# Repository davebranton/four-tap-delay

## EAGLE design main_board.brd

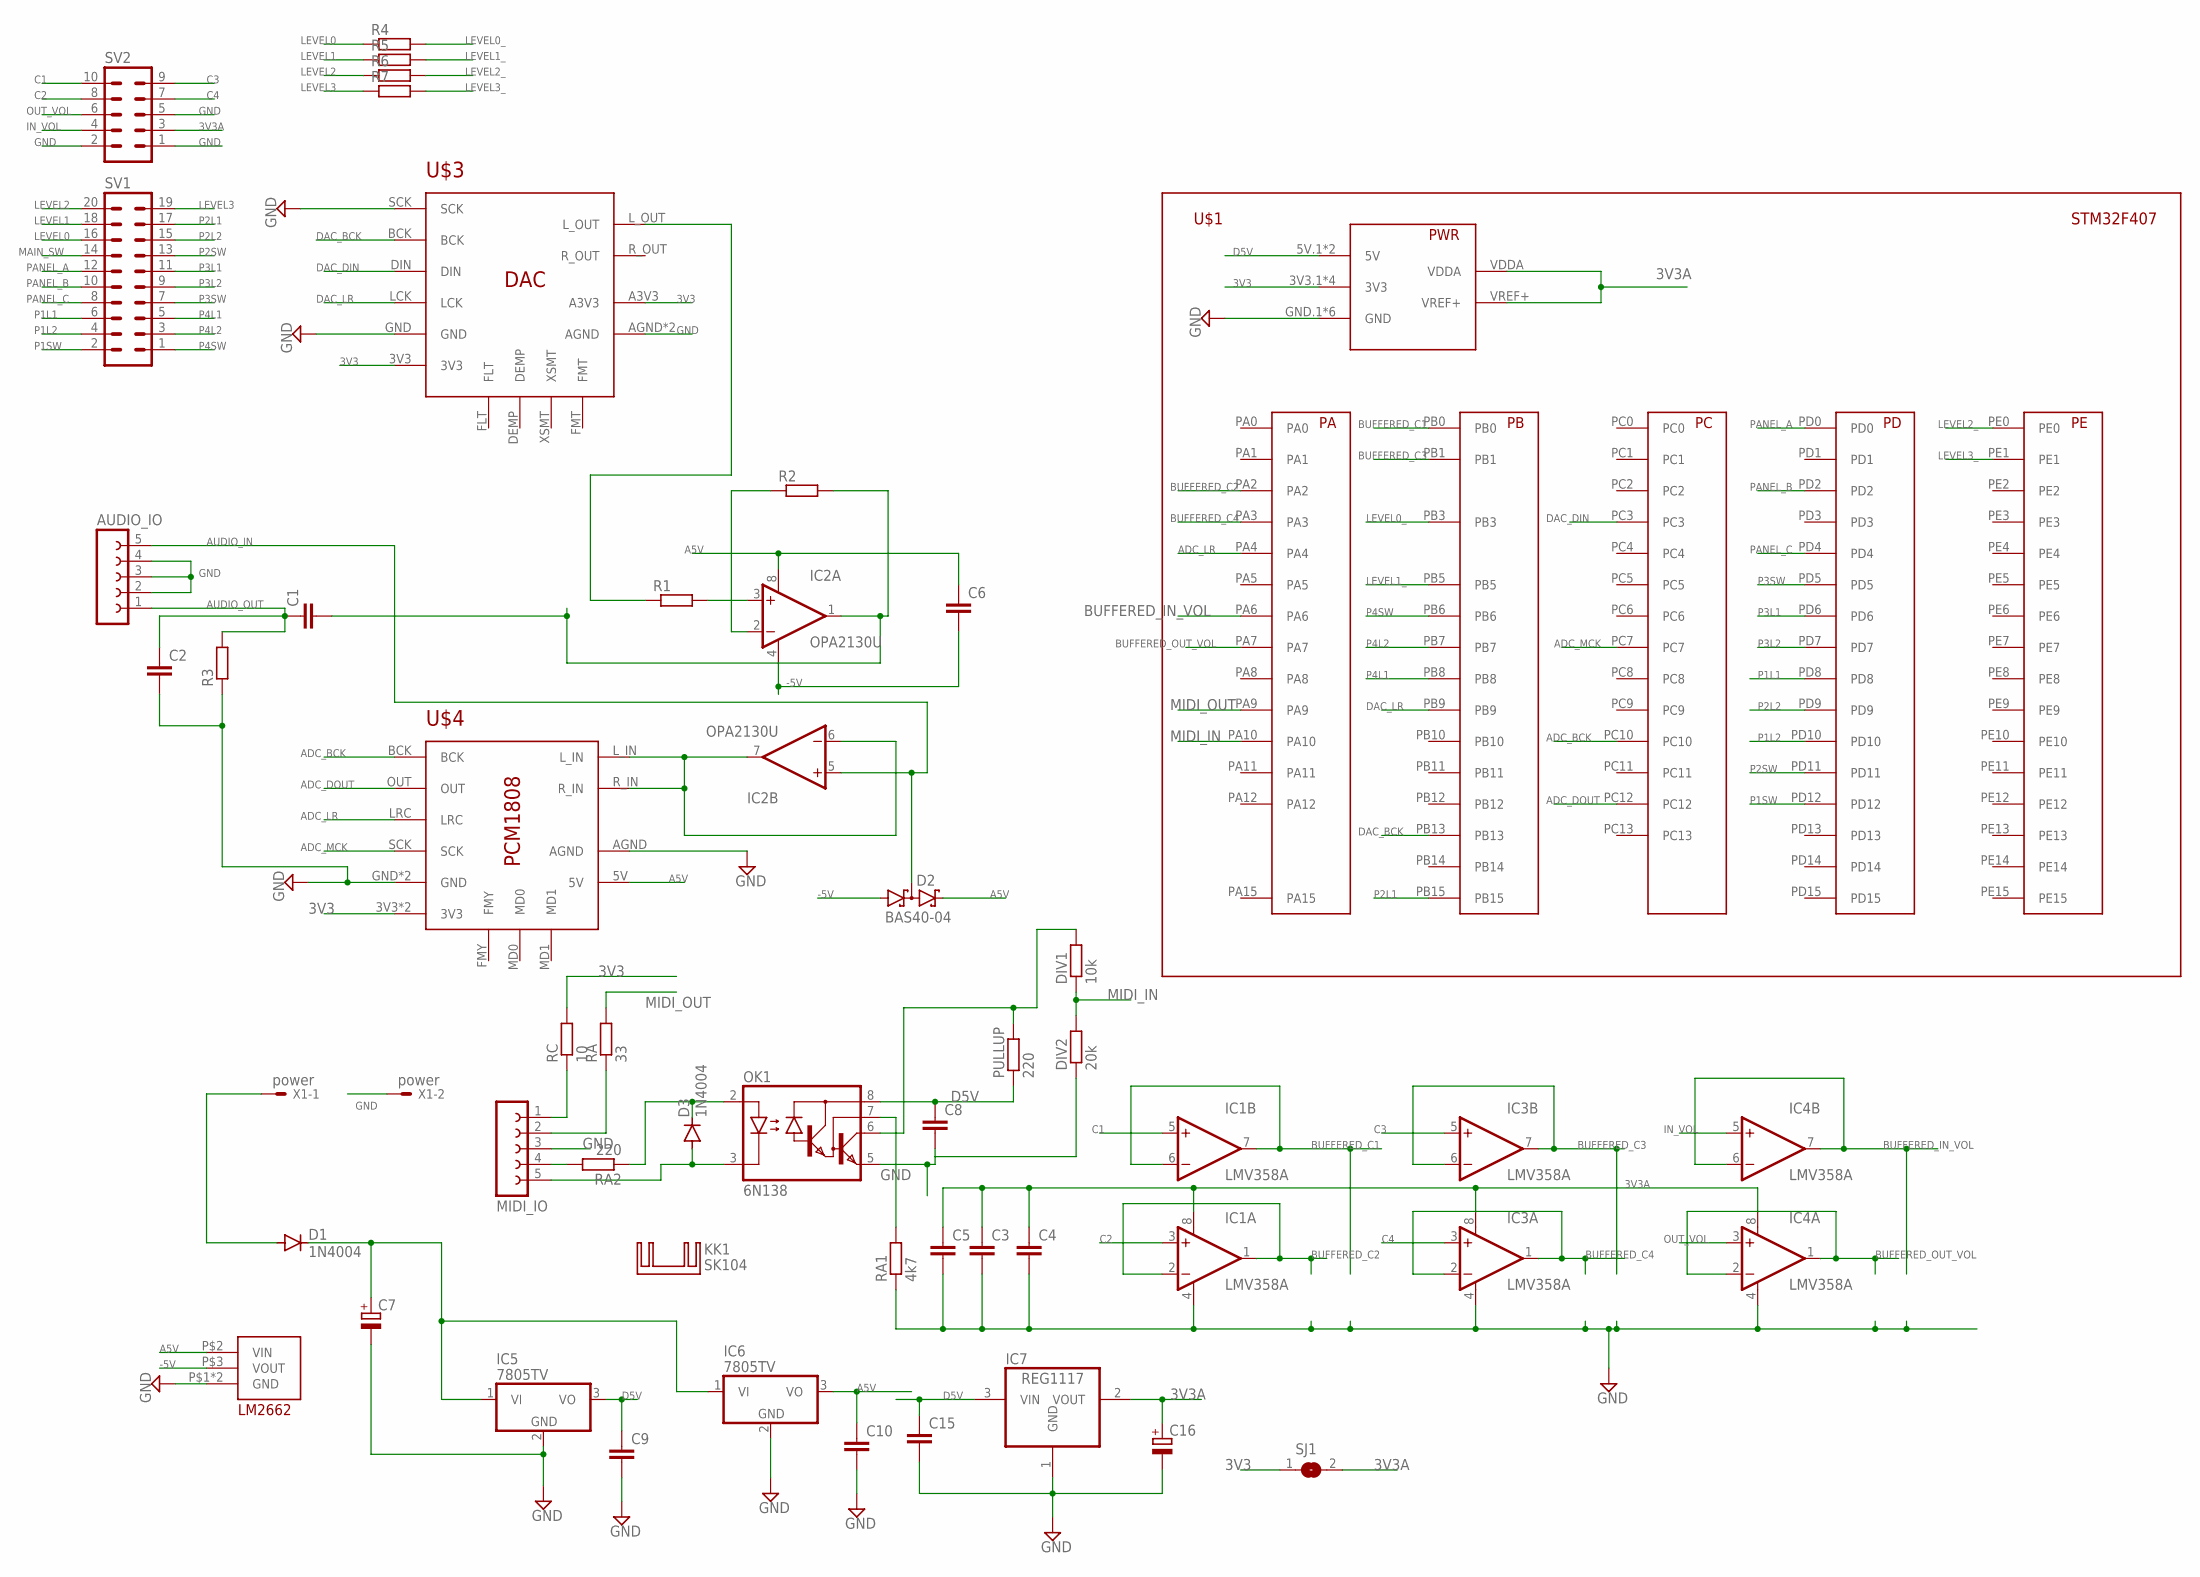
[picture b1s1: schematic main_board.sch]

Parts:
AUDIO_IO: FE05-1
C1: C5/5.5; C5B5.5
C2: C2,5-3; C2.5-3
C3, C4, C5, C6, C15: C-EUC0402; C0402
C7: CPOL-EUE2.5-7; E2,5-7
C8, C9, C10: C-EU025-024X044; C025-024X044
C16: CPOL-EUTT2D6L; TT2D6L
D1, D3: 1N4004; DO41-10
D2: BAS40-04; SOT23
DIV1: 10k; 0204V
DIV2: 20k; 0204V
IC1, IC3, IC4: LMV358A; SO08
IC2: OPA2130U; SO08
IC5, IC6: 7805TV; TO220V
IC7: REG1117; SOT223
KK1: SK104
MIDI_IO: FE05-1
OK1: 6N138; DIL08
PULLUP: 220; 0204V
R1, R2, R3: R-EU_0204/2V; 0204V
R4, R5, R6, R7: R-EU_R0402; R0402
RA: 33; 0204V
RA1: 4k7; 0204V
RA2: 220; 0204V
RC: 10; 0204V
SJ1: SJ
SV1: MA10-2
SV2: MA05-2
U$1: DEVEBOX
U$2: LM2662_MODULE
U$3: PCM510XA; DAC_MODULE
U$4: PCM1808; ADC_MODULE
X1: power; 332-02

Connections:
3V3: RC.2, SJ1.1, U$1.3V3.1 (3V3), U$1.3V3.2 (3V3), U$1.3V3.3 (3V3), U$1.3V3.4 (3V3), U$3.3V3, U$3.A3V3, U$4.3V3, U$4.3V3.1 (3V3)
3V3A: C3.1, C4.1, C5.1, C16.+, IC1.8 (V+), IC3.8 (V+), IC4.8 (V+), IC7.2 (VOUT), SJ1.2, SV2.3, U$1.VDDA, U$1.VREF+
-5V: C6.2, D2.1 (A1), IC2.4 (V-), U$2.P$3 (VOUT)
A5V: C6.1, C10.1, D2.2 (C2), IC2.8 (V+), IC6.3 (VO), U$2.P$2 (VIN), U$4.5V
ADC_BCK: U$1.PC10, U$4.BCK
ADC_DOUT: U$1.PC12, U$4.OUT
ADC_LR: U$1.PA4, U$4.LRC
ADC_MCK: U$1.PC7, U$4.SCK
AUDIO_IN: AUDIO_IO.5, D2.3 (C1A2), IC2.5 (+IN)
AUDIO_OUT: R1.1, U$3.L_OUT
BUFFERED_C1: IC1.6 (-IN), IC1.7 (OUT), U$1.PB0
BUFFERED_C2: IC1.1 (OUT), IC1.2 (-IN), U$1.PA2
BUFFERED_C3: IC3.6 (-IN), IC3.7 (OUT), U$1.PB1
BUFFERED_C4: IC3.1 (OUT), IC3.2 (-IN), U$1.PA3
BUFFERED_IN_VOL: IC4.6 (-IN), IC4.7 (OUT), U$1.PA6
BUFFERED_OUT_VOL: IC4.1 (OUT), IC4.2 (-IN), U$1.PA7
C1: IC1.5 (+IN), SV2.10
C2: IC1.3 (+IN), SV2.8
C3: IC3.5 (+IN), SV2.9
C4: IC3.3 (+IN), SV2.7
D5V: C8.1, C9.1, C15.1, IC5.3 (VO), IC7.3 (VIN), OK1.8 (VCC), PULLUP.1, U$1.5V.1 (5V), U$1.5V.2 (5V)
DAC_BCK: U$1.PB13, U$3.BCK
DAC_DIN: U$1.PC3, U$3.DIN
DAC_LR: U$1.PB9, U$3.LCK
GND: AUDIO_IO.2, AUDIO_IO.3, AUDIO_IO.4, C2.2, C3.2, C4.2, C5.2, C7.-, C8.2, C9.2, C10.2, C15.2, C16.-, DIV2.1, IC1.4 (V-), IC3.4 (V-), IC4.4 (V-), IC5.2 (GND), IC6.2 (GND), IC7.1 (GND), MIDI_IO.3, OK1.5 (GND), R3.1, RA1.1, SV2.1, SV2.2, SV2.5, U$1.GND4. (GND), U$1.GND.1 (GND), U$1.GND.2 (GND), U$1.GND.3 (GND), U$1.GND.6 (GND), U$1.GND.7 (GND), U$2.P$1 (GND), U$2.P$4 (GND), U$3.AGND, U$3.AGND.1 (AGND), U$3.GND, U$3.SCK, U$4.AGND, U$4.GND, U$4.GND.1 (GND), X1.2
IN_VOL: IC4.5 (+IN), SV2.4
LEVEL0: R4.1, SV1.16
LEVEL0_: R4.2, U$1.PB3
LEVEL1: R5.1, SV1.18
LEVEL1_: R5.2, U$1.PB5
LEVEL2: R6.1, SV1.20
LEVEL2_: R6.2, U$1.PE0
LEVEL3: R7.1, SV1.19
LEVEL3_: R7.2, U$1.PE1
MAIN_SW: SV1.14
MIDI_IN: DIV1.1, DIV2.2, U$1.PA10
MIDI_OUT: RA.2, U$1.PA9
unnamed: C7.+, D1.C, IC5.1 (VI), IC6.1 (VI)
unnamed: IC2.6 (-IN), IC2.7 (OUT), U$4.L_IN, U$4.R_IN
unnamed: D1.A, X1.1
unnamed: AUDIO_IO.1, C1.1, C2.1, R3.2
unnamed: D3.A, MIDI_IO.5, OK1.3 (C)
unnamed: D3.C, OK1.2 (A), RA2.1
unnamed: DIV1.2, OK1.6 (VO), PULLUP.2
unnamed: MIDI_IO.1, RC.1
unnamed: MIDI_IO.2, RA.1
unnamed: IC2.3 (+IN), R1.2
unnamed: C1.2, IC2.1 (OUT), R2.2
unnamed: IC2.2 (-IN), R2.1
unnamed: OK1.7 (VB), RA1.2
unnamed: MIDI_IO.4, RA2.2
OUT_VOL: IC4.3 (+IN), SV2.6
P1L1: SV1.6, U$1.PD8
P1L2: SV1.4, U$1.PD10
P1SW: SV1.2, U$1.PD12
P2L1: SV1.17, U$1.PB15
P2L2: SV1.15, U$1.PD9
P2SW: SV1.13, U$1.PD11
P3L1: SV1.11, U$1.PD6
P3L2: SV1.9, U$1.PD7
P3SW: SV1.7, U$1.PD5
P4L1: SV1.5, U$1.PB8
P4L2: SV1.3, U$1.PB7
P4SW: SV1.1, U$1.PB6
PANEL_A: SV1.12, U$1.PD0
PANEL_B: SV1.10, U$1.PD2
PANEL_C: SV1.8, U$1.PD4

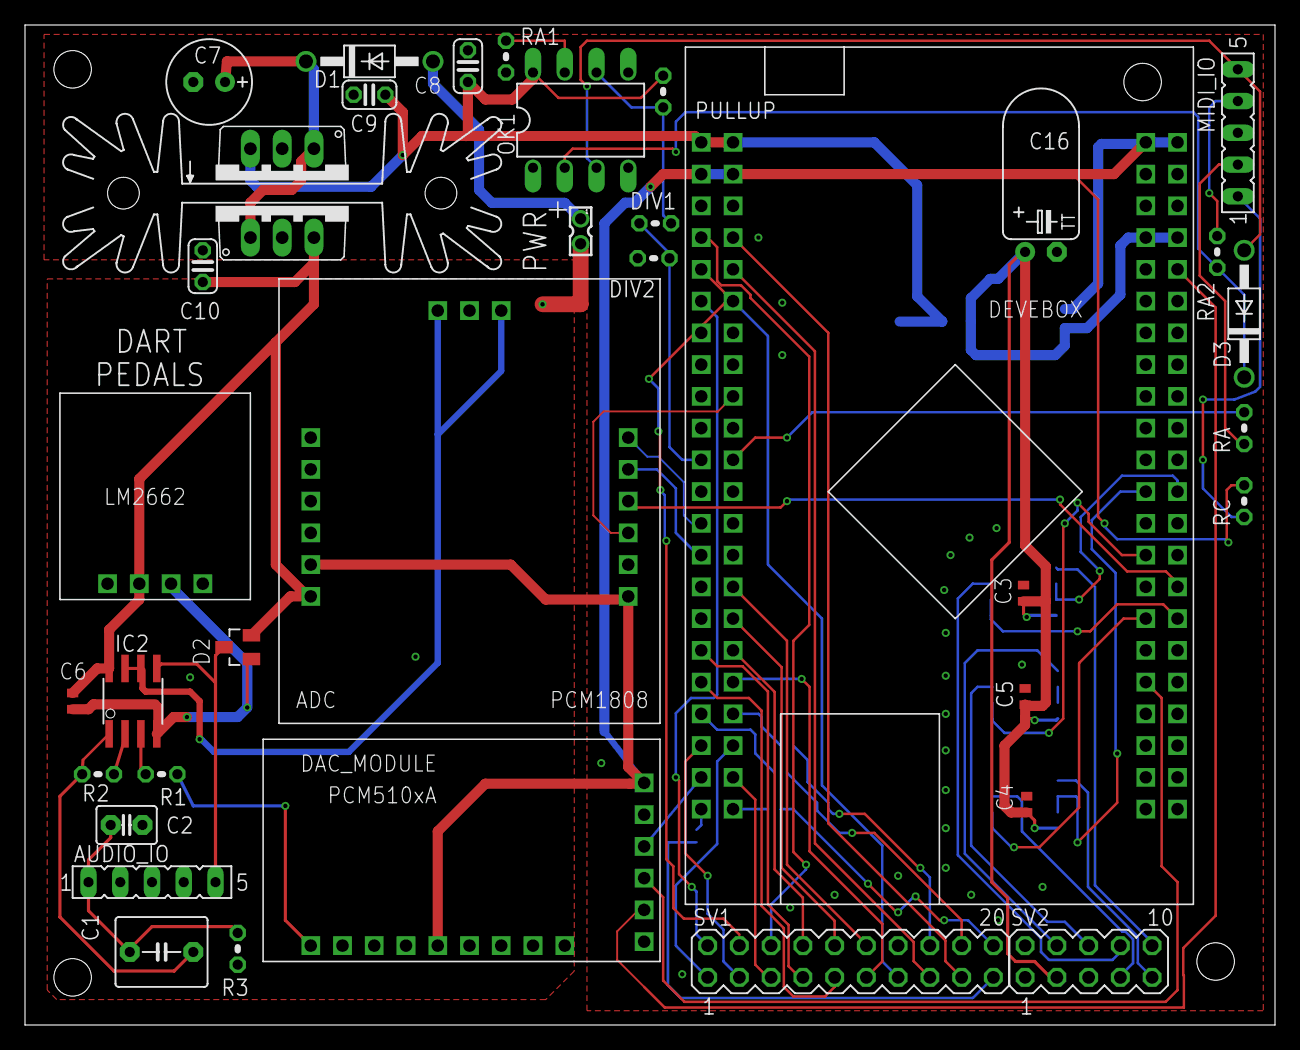
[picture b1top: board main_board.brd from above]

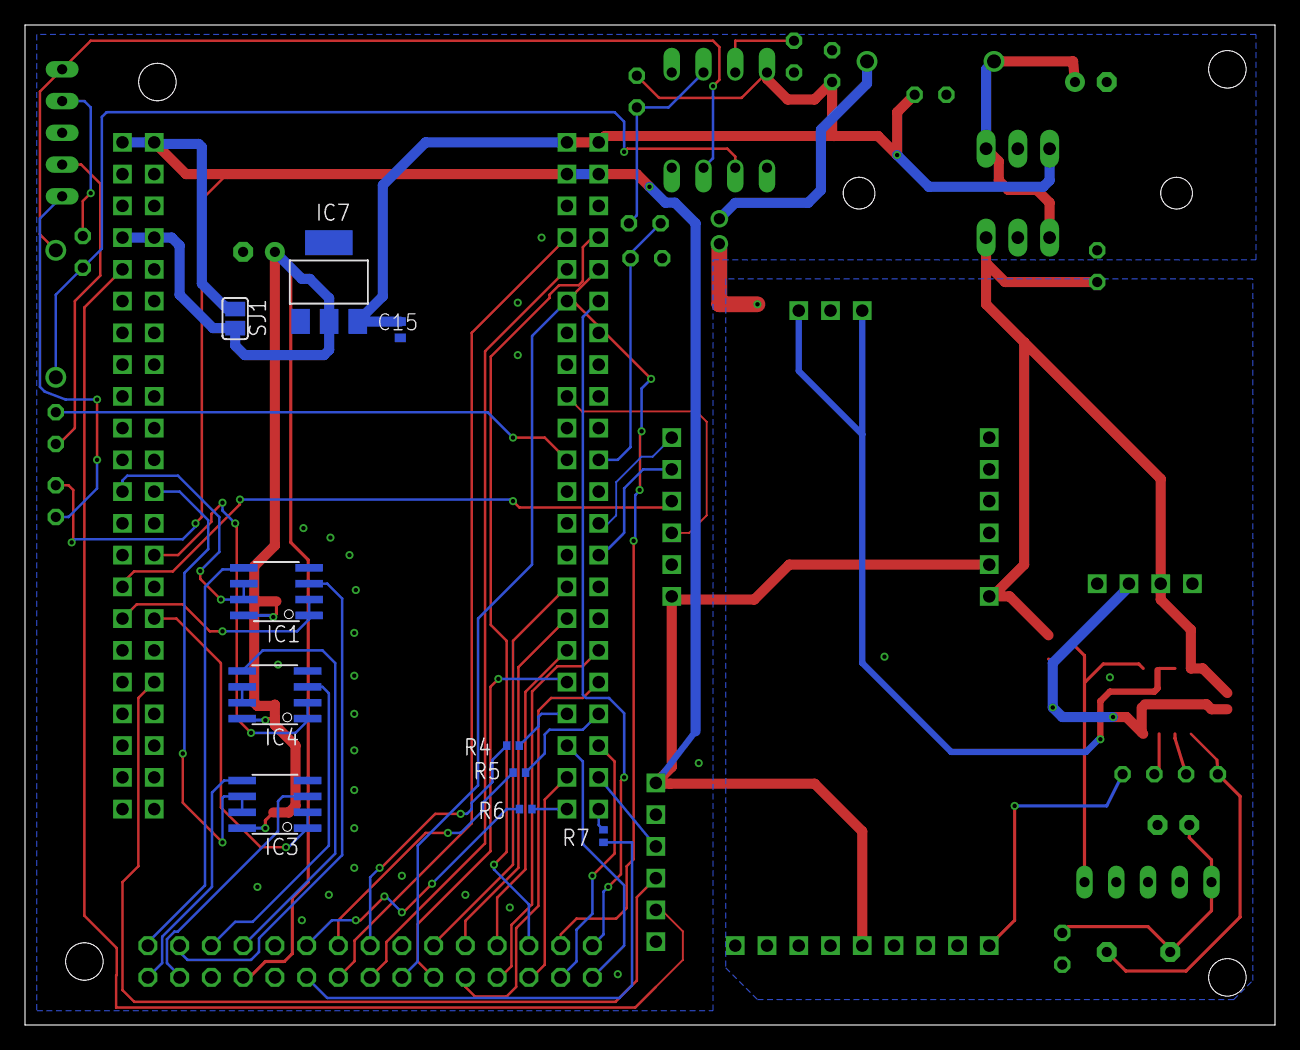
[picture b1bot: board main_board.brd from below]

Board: 2 copper layers, 100.0 x 80.0 mm, 48 parts (10 on the bottom side), 66 nets.

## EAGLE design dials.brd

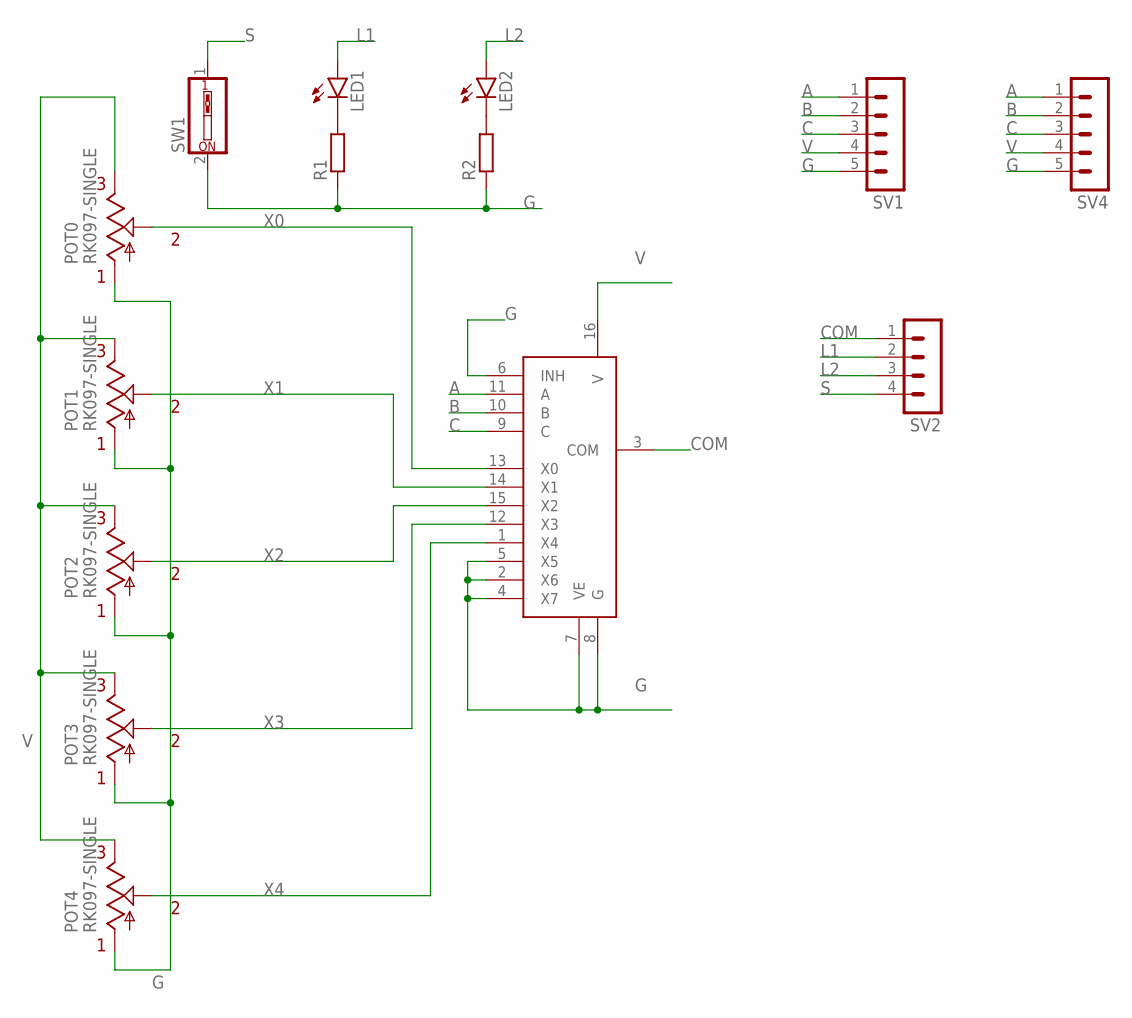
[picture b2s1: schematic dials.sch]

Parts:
LED1, LED2: LED3MM
POT0, POT1, POT2, POT3, POT4: RK097-SINGLE; RK097-SINGLE-ELEMENT
R1, R2: R-EU_0204/7; 0204/7
SV1, SV4: MA05-1
SV2: MA04-1
SW1: SW_DIP-1; EDG-01
U$6: MC14051; DIP16

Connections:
A: SV1.1, SV4.1, U$6.11 (A)
B: SV1.2, SV4.2, U$6.10 (B)
C: SV1.3, SV4.3, U$6.9 (C)
COM: SV2.1, U$6.3 (COM)
G: POT0.P$4 (A), POT1.P$4 (A), POT2.P$4 (A), POT3.P$4 (A), POT4.P$4 (A), R1.1, R2.1, SV1.5, SV4.5, SW1.2, U$6.2 (X6), U$6.4 (X7), U$6.5 (X5), U$6.6 (INH), U$6.7 (VE), U$6.8 (G)
L1: LED1.A, SV2.2
L2: LED2.A, SV2.3
unnamed: LED1.K (C), R1.2
unnamed: LED2.K (C), R2.2
S: SV2.4, SW1.1
V: POT0.P$6 (E), POT1.P$6 (E), POT2.P$6 (E), POT3.P$6 (E), POT4.P$6 (E), SV1.4, SV4.4, U$6.16 (V)
X0: POT0.P$5 (S), U$6.13 (X0)
X1: POT1.P$5 (S), U$6.14 (X1)
X2: POT2.P$5 (S), U$6.15 (X2)
X3: POT3.P$5 (S), U$6.12 (X3)
X4: POT4.P$5 (S), U$6.1 (X4)

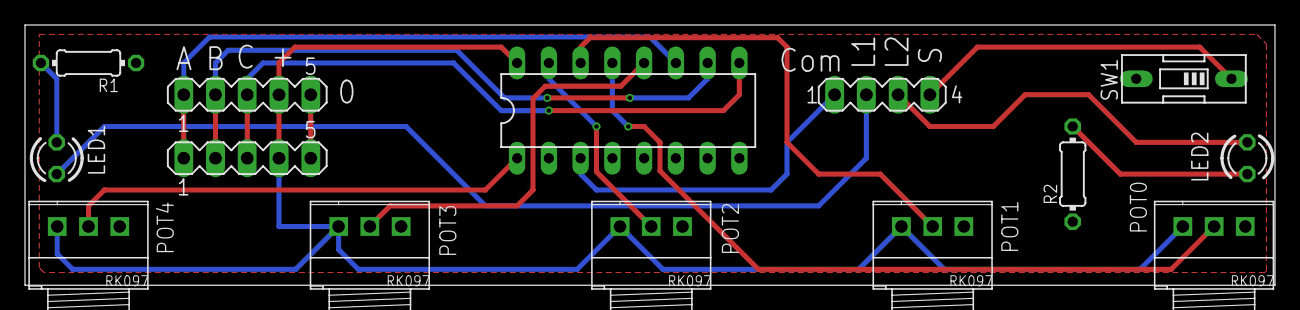
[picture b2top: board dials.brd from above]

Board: 2 copper layers, 100.0 x 20.8 mm, 14 parts (0 on the bottom side), 16 nets.

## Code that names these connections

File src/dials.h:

#include <stdint.h>
#include <array>

#pragma once

#include "stm32f4xx_conf.h"
#include "ports.h"

int16_t Cal(int32_t uncal_value)
{
  // Maybe due to buffers, we see about 50 - 4060 instead of 0 - 4096
  uncal_value -= 50;
  if (uncal_value < 0) return 0;
  uncal_value = (uncal_value * 4010) / 4046;
  if (uncal_value > 0xFFF) return 0xFFF;
  return uncal_value;
}

template<int bits>
class MovingAverageFilter
{
  int i = 0;
  int16_t v[1 << bits];
  int32_t total = 0;
  int32_t frozen_total = 0;
  
  public: 
  int midi_value = -1;
  volatile int16_t last_v;
  MovingAverageFilter()
  {
    for(int i = 0; i < (1<<bits); i++) v[i] = 0;
  }
  void SetMidiValue(int16_t mv) {
    frozen_total = total;
    midi_value = mv;
  }
  int16_t GetValue() { 
    if (midi_value == -1)
    {
      return (total >> bits);
    }
    else
    {
      if (frozen_total > 0 && abs(frozen_total - total) > (3 << bits))
      {
        midi_value = -1;
        return (total >> bits);
      }
      return  midi_value;
    }
  }
  void NewValue(int16_t _v) { 
    last_v = _v;
    total += _v;
    total -= v[i];
    v[i] = _v; 
    i++; if (i==(1<<bits)) i = 0;
  }
};

using DialFilter = MovingAverageFilter<8>;


DialFilter output_volume;
DialFilter input_volume;
std::array<std::array<DialFilter,5>,4> dial_panel;

template <typename A, typename B, typename C>
class DialBank
{
public:

  uint8_t index = 0;

  void Setup()
  {
    A::Output();
    B::Output();
    C::Output();
  }

  void SetBits()
  {
    auto _index = index;
    if (_index & 1) A::Set(); else A::Reset();
    if (_index & 2) B::Set(); else B::Reset();
    if (_index & 4) C::Set(); else C::Reset();
  }

  void Next()
  {
    index++;
    if (index == 5) index = 0;
    SetBits();
  }
};

volatile uint16_t DMA_values[8];
DialBank<Dials_A, Dials_B, Dials_C> dial_counter;

void init_dial_readers()
{  
  GpioE::Port<0>::Output();

  dial_counter.Setup();

  // Power on the ADC for the dials  
  ADC_InitTypeDef adc_init;
  adc_init.ADC_Resolution = ADC_Resolution_12b;
  adc_init.ADC_ScanConvMode = ENABLE;
  adc_init.ADC_ContinuousConvMode = ENABLE;
  adc_init.ADC_ExternalTrigConvEdge = ADC_ExternalTrigConvEdge_None;
  adc_init.ADC_ExternalTrigConv = 0;
  adc_init.ADC_DataAlign = ADC_DataAlign_Right;
  adc_init.ADC_NbrOfConversion = 8;
  ADC_Init(ADC1, &adc_init);

  // 
  ADC1->CR2 |= ADC_CR2_DDS;

  DMA_values[0] = 0;
  DMA_values[1] = 0;
  DMA_values[2] = 0;
  DMA_values[3] = 0;
  DMA_values[4] = 0;
  DMA_values[5] = 0;
  DMA_values[6] = 0;
  DMA_values[7] = 0;

  // Seven channels in order

  GpioB::Port<0>::Analog(); // ADC_Channel_8
  GpioA::Port<2>::Analog(); // ADC_Channel_2
  GpioB::Port<1>::Analog(); // ADC_Channel_9
  GpioA::Port<3>::Analog(); // ADC_Channel_3
  GpioA::Port<7>::Analog(); // ADC_Channel_7
  GpioA::Port<6>::Analog(); // ADC_Channel_6
  ADC_RegularChannelConfig(ADC1, ADC_Channel_Vbat, 1, ADC_SampleTime_144Cycles); // this one here so we ignore transition to the next multiplex output
  ADC_RegularChannelConfig(ADC1, ADC_Channel_Vbat, 2, ADC_SampleTime_144Cycles); // this one here so we ignore transition to the next multiplex output
  ADC_RegularChannelConfig(ADC1, ADC_Channel_8, 3, ADC_SampleTime_144Cycles); //  PB0
  ADC_RegularChannelConfig(ADC1, ADC_Channel_2, 4, ADC_SampleTime_144Cycles); //  PA2
  ADC_RegularChannelConfig(ADC1, ADC_Channel_9, 5, ADC_SampleTime_144Cycles); //  PB1
  ADC_RegularChannelConfig(ADC1, ADC_Channel_3, 6, ADC_SampleTime_144Cycles); //  PA3
  ADC_RegularChannelConfig(ADC1, ADC_Channel_6, 7, ADC_SampleTime_144Cycles); //  PA7 // in vol
  ADC_RegularChannelConfig(ADC1, ADC_Channel_7, 8, ADC_SampleTime_144Cycles); //  PA6 // out vol

  // Common init for the clock
  ADC_CommonInitTypeDef adc_common_init;
  ADC_CommonStructInit(&adc_common_init);
  adc_common_init.ADC_Prescaler = ADC_Prescaler_Div8;
  // setting this stops the EOC interrupt for some reason
  //adc_common_init.ADC_DMAAccessMode = ADC_DMAAccessMode_1;
  ADC_CommonInit(&adc_common_init);

  // Turn on DMA
  // DMA 2 Stream 4 set to Channel 0 for ADC1
  
  DMA_InitTypeDef dma;
  dma.DMA_Channel = DMA_Channel_0;
  dma.DMA_PeripheralBaseAddr = (uint32_t)&(ADC1->DR);
  dma.DMA_Memory0BaseAddr = (uint32_t)DMA_values;
  dma.DMA_DIR = DMA_DIR_PeripheralToMemory;
  dma.DMA_BufferSize = 8; 
  dma.DMA_PeripheralInc = DMA_PeripheralInc_Disable;
  dma.DMA_MemoryInc = DMA_MemoryInc_Enable;
  dma.DMA_PeripheralDataSize = DMA_PeripheralDataSize_HalfWord;
  dma.DMA_MemoryDataSize = DMA_MemoryDataSize_HalfWord;
  dma.DMA_Mode = DMA_Mode_Circular;
  dma.DMA_Priority = DMA_Priority_Medium;
  dma.DMA_FIFOMode = DMA_FIFOMode_Disable;
  dma.DMA_FIFOThreshold = 0;
  dma.DMA_MemoryBurst = DMA_MemoryBurst_Single;
  dma.DMA_PeripheralBurst = DMA_PeripheralBurst_Single;

  DMA_Init(DMA2_Stream4, &dma);
  DMA_Cmd(DMA2_Stream4, ENABLE);
  ADC_DMACmd(ADC1, ENABLE); // enabling DMA stop the EOC interrupt??

  // transfer complete and also half complete
  DMA2_Stream4->CR |=  DMA_SxCR_TCIE | DMA_SxCR_HTIE;

  NVIC_EnableIRQ(DMA2_Stream4_IRQn);  
  NVIC_SetPriority(DMA2_Stream4_IRQn, 2);
  ADC_Cmd(ADC1, ENABLE);
  //ADC_ITConfig(ADC1, ADC_IT_EOC, ENABLE);
  ADC_SoftwareStartConv(ADC1); // ADC1 is in continous mode, and will convert from now on.
GpioE::Port<0>::Reset();

}

// Must be volatile or some kind of caching kills us
volatile uint16_t read_dials[6];

extern "C" void DMA2_Stream4_IRQHandler()
{
  //GpioE::Port<0>::Set();
  if (DMA2->HISR & DMA_HISR_TCIF4)
  {
    // complete
    GpioE::Port<0>::Set();
    auto counterval = dial_counter.index;
    dial_counter.Next();
    read_dials[2] = DMA_values[4];
    read_dials[3] = DMA_values[5];
    read_dials[4] = DMA_values[6];
    read_dials[5] = DMA_values[7];
    DMA2->HIFCR |= DMA_HIFCR_CTCIF4;   

    // We get in here at ~20kHz
    
    // We now have a set of analog reads, from the dials
    for(int i = 0; i < 4; i++)
    {
      // they're all backwards... so subtrack from 4095
      dial_panel[i][counterval].NewValue(4095 - read_dials[i]);
    }
    
    // and the volumes
    input_volume.NewValue(read_dials[4]);    
    output_volume.NewValue(read_dials[5]);
    
    GpioE::Port<0>::Reset();
  }
  if (DMA2->HISR & DMA_HISR_HTIF4)
  {
    // half complete
    //read_dials[0] = DMA_values[0]; don't need this value
    read_dials[0] = DMA_values[2];
    read_dials[1] = DMA_values[3];
    DMA2->HIFCR |= DMA_HIFCR_CHTIF4;
  }
  //GpioE::Port<0>::Reset();
  
}
